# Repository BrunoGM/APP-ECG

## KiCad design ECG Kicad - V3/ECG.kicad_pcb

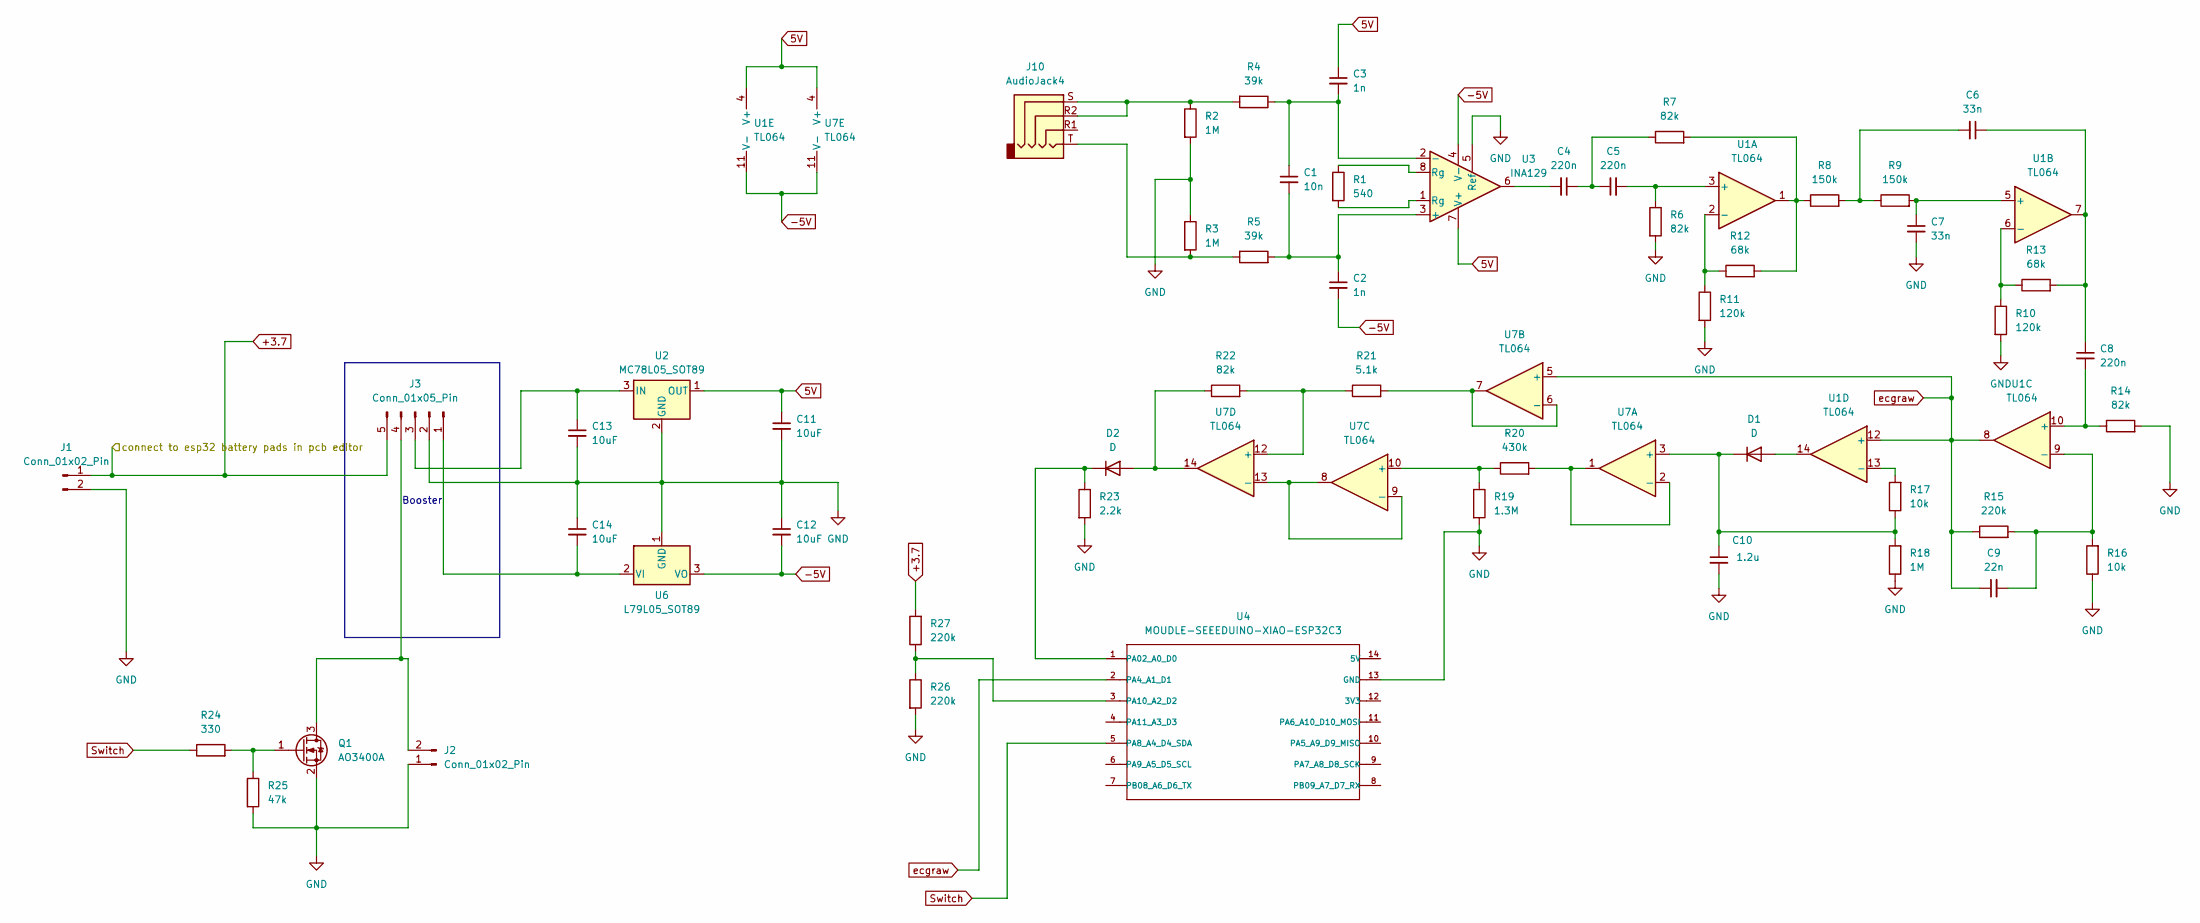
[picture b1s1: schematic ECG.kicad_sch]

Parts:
C1: 10n; C_0805_2012Metric
C2, C3: 1n; C_0805_2012Metric
C4, C5, C8: 220n; C_0805_2012Metric
C6, C7: 33n; C_0805_2012Metric
C9: 22n; C_0805_2012Metric
C10: 1.2u; C_0805_2012Metric
C11, C12, C13, C14: 10uF; C_0805_2012Metric
D1, D2: D; Nexperia_CFP3_SOD-123W
J1, J2: Conn_01x02_Pin; PinHeader_1x02_P2.54mm_Vertical
J3: Conn_01x05_Pin; PinHeader_1x05_P2.54mm_Vertical
J10: AudioJack4; Jack_3.5mm_KoreanHropartsElec_PJ-320D-4A_Horizontal
Q1: AO3400A; SOT-23
R1: 540; R_0805_2012Metric
R2, R3, R18: 1M; R_0805_2012Metric
R4, R5: 39k; R_0805_2012Metric
R6, R7, R14, R22: 82k; R_0805_2012Metric
R8, R9: 150k; R_0805_2012Metric
R10, R11: 120k; R_0805_2012Metric
R12, R13: 68k; R_0805_2012Metric
R15, R26, R27: 220k; R_0805_2012Metric
R16, R17: 10k; R_0805_2012Metric
R19: 1.3M; R_0805_2012Metric
R20: 430k; R_0805_2012Metric
R21: 5.1k; R_0805_2012Metric
R23: 2.2k; R_0805_2012Metric
R24: 330; R_0805_2012Metric
R25: 47k; R_0805_2012Metric
U1, U7: TL064; SOIC-14_3.9x8.7mm_P1.27mm
U2: MC78L05_SOT89; SOT-89-3
U3: INA129; DIP-8_W7.62mm
U4: MOUDLE-SEEEDUINO-XIAO-ESP32C3; MCU_Seeed_ESP32C3
U6: L79L05_SOT89; SOT-89-3

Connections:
5V: C3.1, C11.1, U1.4 (V+), U2.1 (OUT), U3.7 (V+), U7.4 (V+)
+3.7: J1.1, J3.5, R27.2
-5V: C2.2, C12.2, U1.11 (V-), U3.4 (V-), U6.3 (VO), U7.11 (V-)
GND: C7.2, C10.2, C11.2, C12.1, C13.2, C14.1, J1.2, J2.1, J3.2, Q1.2 (S), R2.2, R3.1, R6.2, R10.2, R11.2, R14.2, R16.1, R18.1, R19.2, R23.2, R25.2, R26.2, U2.2 (GND), U3.5 (Ref), U4.13 (GND), U6.1 (GND)
unnamed: C4.1, C5.1, R7.1
unnamed: C4.2, U3.6
unnamed: C6.1, C8.1, R13.2, U1.7
unnamed: C6.2, R8.2, R9.1
unnamed: D1.2 (A), U1.14
unnamed: C10.1, D1.1 (K), R17.1, R18.2, U7.3 (+)
unnamed: D2.2 (A), R22.1, U7.14
unnamed: D2.1 (K), R23.1, U4.1 (PA02_A0_D0)
unnamed: J2.2, J3.4, Q1.3 (D)
unnamed: C14.2, J3.1, U6.2 (VI)
unnamed: C13.1, J3.3, U2.3 (IN)
unnamed 15: J10.R2, J10.S, R2.1, R4.2; also elsewhere on the board
unnamed 16: J10.T, R3.2, R5.1; also elsewhere on the board
unnamed: Q1.1 (G), R24.2, R25.1
unnamed: R1.1, U3.8 (Rg)
unnamed: R1.2, U3.1 (Rg)
unnamed: R7.2, R8.1, R12.2, U1.1
unnamed: C5.2, R6.1, U1.3 (+)
unnamed: R11.1, R12.1, U1.2 (-)
unnamed: C7.1, R9.2, U1.5 (+)
unnamed: R10.1, R13.1, U1.6 (-)
unnamed: C8.2, R14.1, U1.10 (+)
unnamed: C9.2, R15.2, R16.2, U1.9 (-)
unnamed: R17.2, U1.13 (-)
unnamed: C1.2, C2.1, R5.2, U3.3 (+)
unnamed: C1.1, C3.2, R4.1, U3.2 (-)
unnamed: R26.1, R27.1, U4.3 (PA10_A2_D2)
unnamed: R20.2, U7.1, U7.2 (-)
unnamed: R21.2, U7.6 (-), U7.7
unnamed: R19.1, R20.1, U7.10 (+)
unnamed: U7.8, U7.9 (-), U7.13 (-)
unnamed: R21.1, R22.2, U7.12 (+)
Switch: R24.1, U4.5 (PA8_A4_D4_SDA)
ecgraw: C9.1, R15.1, U1.8, U1.12 (+), U4.2 (PA4_A1_D1), U7.5 (+)

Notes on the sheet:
Booster

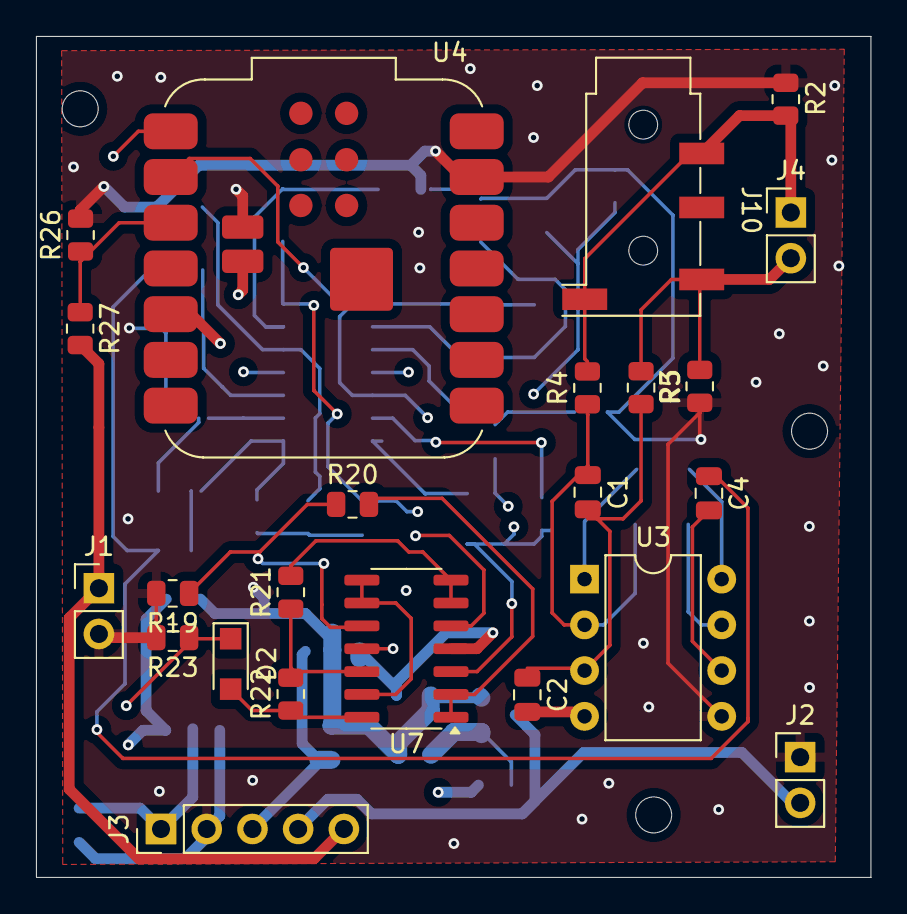
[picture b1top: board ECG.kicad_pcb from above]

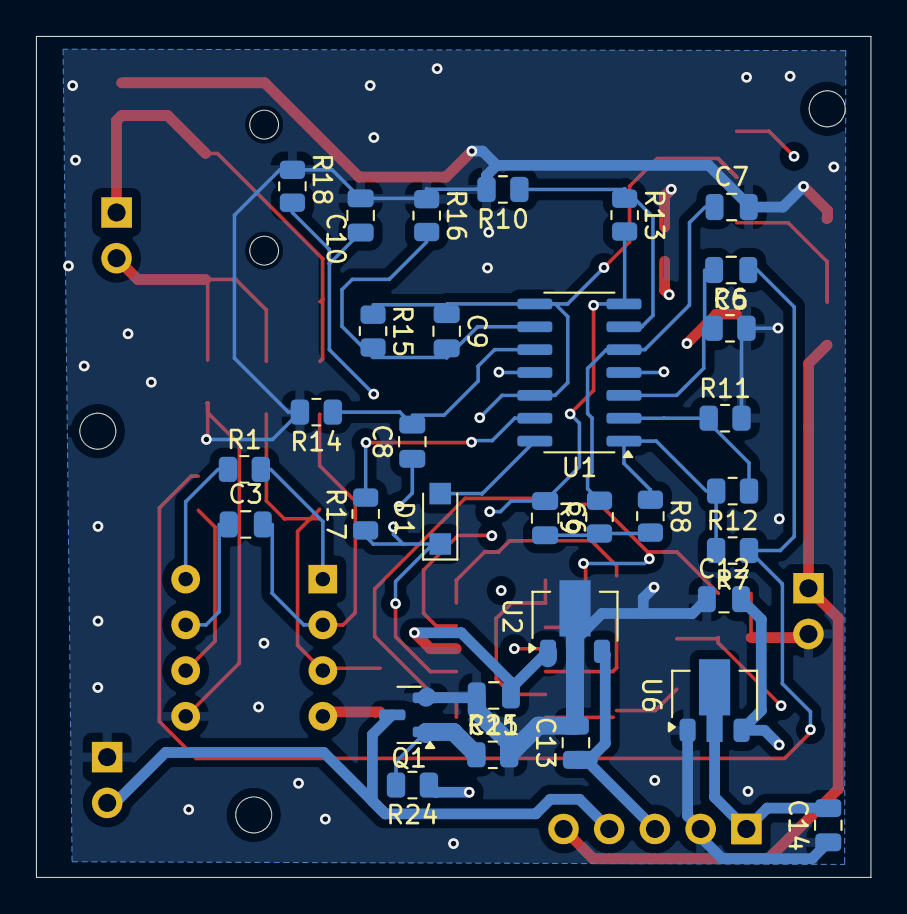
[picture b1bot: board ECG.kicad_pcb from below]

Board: 4 copper layers, 46.4 x 46.7 mm, 55 parts (32 on the bottom side), 38 nets.

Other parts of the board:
J4: Conn_01x02_Pin; PinHeader_1x02_P2.54mm_Vertical

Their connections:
unnamed 15: J4.1; also elsewhere on the board
unnamed 16: J4.2; also elsewhere on the board

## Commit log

2025-03-20 1
    1
